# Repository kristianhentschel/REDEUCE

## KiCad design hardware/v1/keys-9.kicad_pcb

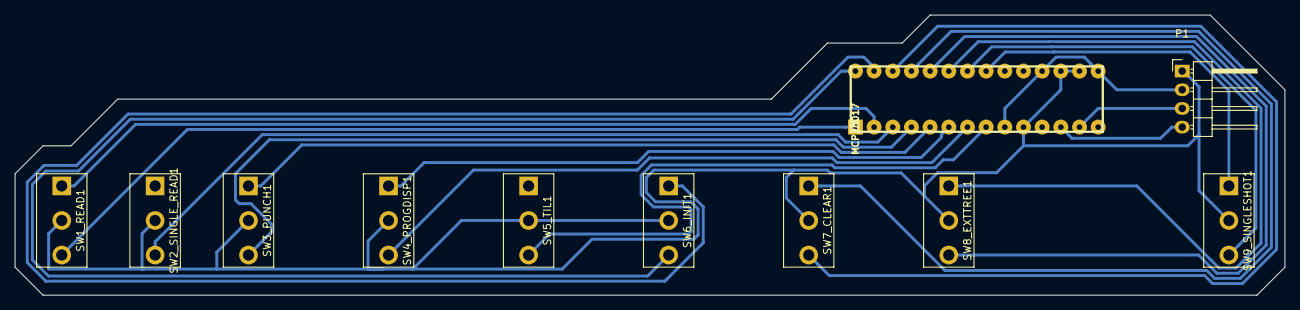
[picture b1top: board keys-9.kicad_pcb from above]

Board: 2 copper layers, 172.7 x 38.1 mm, 11 parts (0 on the bottom side), 20 nets.

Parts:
P1: CONN_01X04; Pin_Header_Angled_1x04
SW1_READ1, SW2_SINGLE_READ1, SW3_PUNCH1, SW4_PROGDISP1, SW5_TIL1, SW6_INIT1, SW7_CLEAR1, SW8_EXTTREE1, SW9_SINGLESHOT1: SWITCH_INV; SW_SPDT-custom
U1: MCP23017; DIL28

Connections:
/CLEAR_A: SW7_CLEAR1.3, U1.26
/CLEAR_B: SW7_CLEAR1.1, U1.25
/EXTREE_A: SW8_EXTTREE1.1, U1.23
/EXTREE_B: SW8_EXTTREE1.3, U1.24
/INIT_A: SW6_INIT1.1, U1.27
/INIT_B: SW6_INIT1.3, U1.28
/PROGDISP_A: SW4_PROGDISP1.3, U1.7
/PROGDISP_B: SW4_PROGDISP1.1, U1.6
/PUNCH_A: SW3_PUNCH1.1, U1.5
/PUNCH_B: SW3_PUNCH1.3, U1.4
/READ_A: SW1_READ1.1, U1.2
/READ_B: SW1_READ1.3, U1.1
/SCK: P1.4, U1.12
/SDA: P1.3, U1.13
/SINGLE_A: SW9_SINGLESHOT1.1, U1.21
/SINGLE_B: SW9_SINGLESHOT1.3, U1.22
/SREAD_DOWN: SW2_SINGLE_READ1.3, U1.3
/TIL_DOWN: SW5_TIL1.3, U1.8
GND: P1.1, SW1_READ1.2, SW2_SINGLE_READ1.2, SW3_PUNCH1.2, SW4_PROGDISP1.2, SW5_TIL1.2, SW6_INIT1.2, SW7_CLEAR1.2, SW8_EXTTREE1.2, SW9_SINGLESHOT1.2, U1.10, U1.16, U1.17
VDD: P1.2, U1.9, U1.15, U1.18

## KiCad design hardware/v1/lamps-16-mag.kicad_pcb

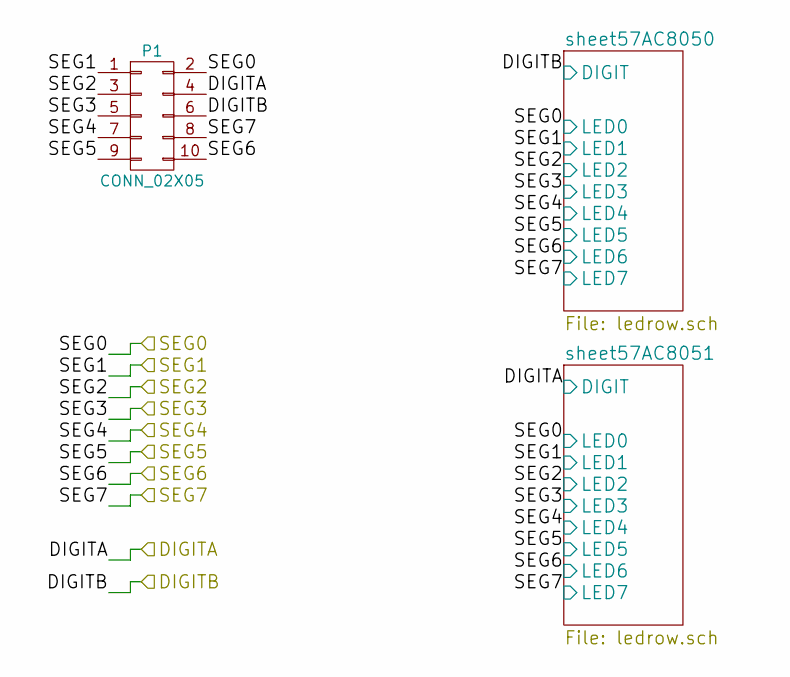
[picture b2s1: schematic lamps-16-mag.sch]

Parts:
P1: CONN_02X05; Pin_Header_Straight_2x05

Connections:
/DIGITA: P1.4; also elsewhere on the board
/DIGITB: P1.6; also elsewhere on the board
/SEG0: P1.2; also elsewhere on the board
/SEG1: P1.1; also elsewhere on the board
/SEG2: P1.3; also elsewhere on the board
/SEG3: P1.5; also elsewhere on the board
/SEG4: P1.7; also elsewhere on the board
/SEG5: P1.9; also elsewhere on the board
/SEG6: P1.10; also elsewhere on the board
/SEG7: P1.8; also elsewhere on the board

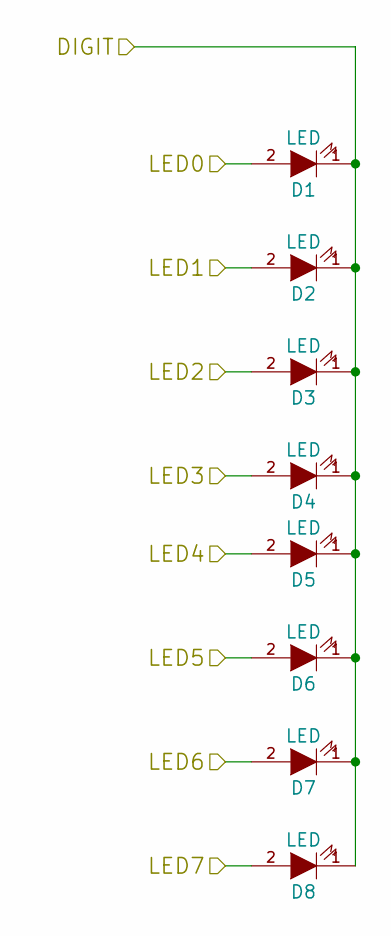
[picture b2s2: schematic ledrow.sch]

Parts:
D1, D2, D3, D4, D5, D6, D7, D8: LED; LED-5MM-custom

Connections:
/DIGITB: D1.1 (K), D2.1 (K), D3.1 (K), D4.1 (K), D5.1 (K), D6.1 (K), D7.1 (K), D8.1 (K); also elsewhere on the board
/SEG0: D1.2 (A); also elsewhere on the board
/SEG1: D2.2 (A); also elsewhere on the board
/SEG2: D3.2 (A); also elsewhere on the board
/SEG3: D4.2 (A); also elsewhere on the board
/SEG4: D5.2 (A); also elsewhere on the board
/SEG5: D6.2 (A); also elsewhere on the board
/SEG6: D7.2 (A); also elsewhere on the board
/SEG7: D8.2 (A); also elsewhere on the board

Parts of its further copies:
D9, D10, D11, D12, D13, D14, D15, D16: LED; LED-5MM-custom

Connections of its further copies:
/DIGITA: D9.1 (K), D10.1 (K), D11.1 (K), D12.1 (K), D13.1 (K), D14.1 (K), D15.1 (K), D16.1 (K); also elsewhere on the board
/SEG0: D9.2 (A); also elsewhere on the board
/SEG1: D10.2 (A); also elsewhere on the board
/SEG2: D11.2 (A); also elsewhere on the board
/SEG3: D12.2 (A); also elsewhere on the board
/SEG4: D13.2 (A); also elsewhere on the board
/SEG5: D14.2 (A); also elsewhere on the board
/SEG6: D15.2 (A); also elsewhere on the board
/SEG7: D16.2 (A); also elsewhere on the board

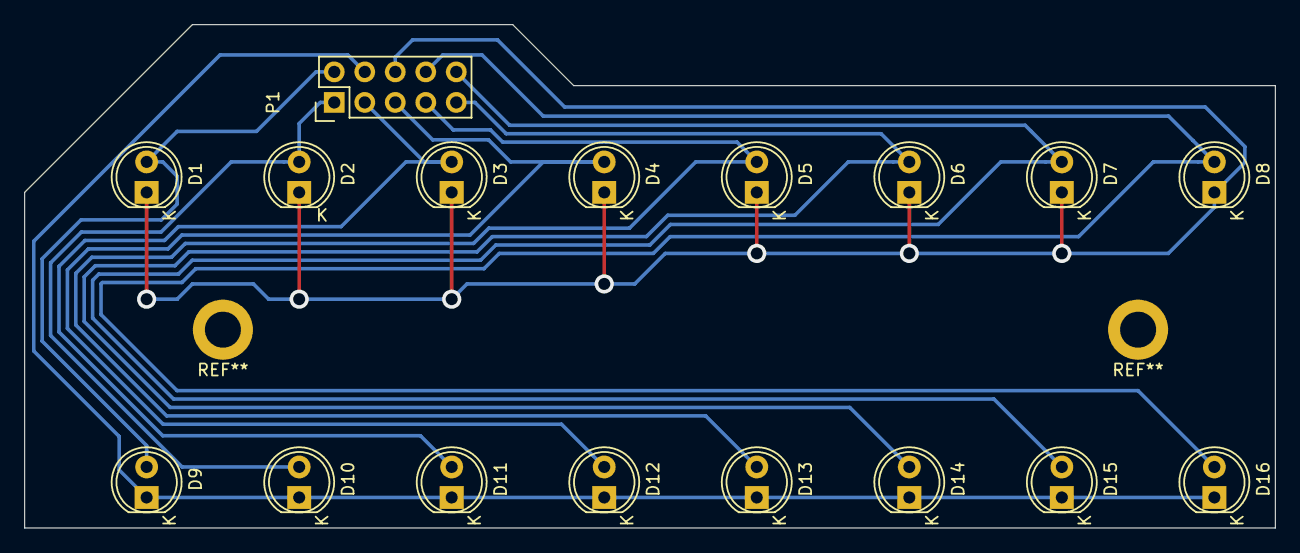
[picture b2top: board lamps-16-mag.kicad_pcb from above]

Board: 2 copper layers, 104.1 x 41.9 mm, 17 parts (0 on the bottom side), 10 nets.

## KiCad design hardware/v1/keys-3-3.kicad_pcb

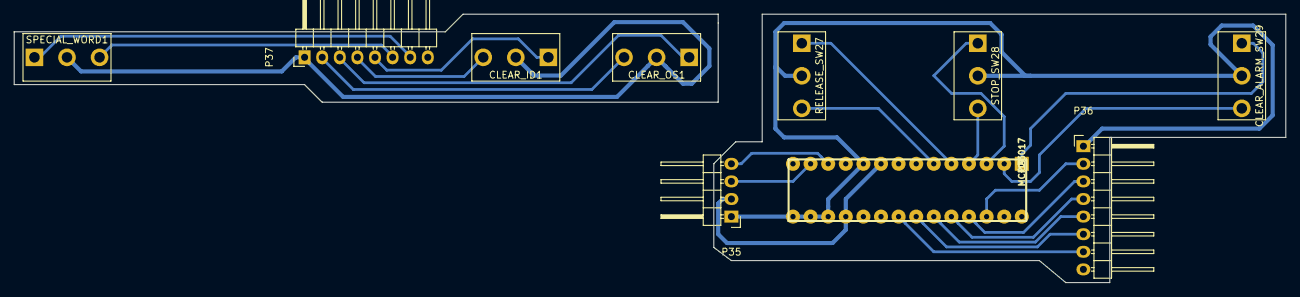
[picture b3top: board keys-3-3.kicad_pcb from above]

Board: 2 copper layers, 183.5 x 38.7 mm, 10 parts (0 on the bottom side), 23 nets.

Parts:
CLEAR_ALARM_SW29: SWITCH_INV; SW_SPDT-custom
CLEAR_ID1: SWITCH_INV; SW_SPDT-custom
CLEAR_OS1: SWITCH_INV; SW_SPDT-custom
P35: CONN_01X04; Pin_Header_Angled_1x04
P36, P37: CONN_01X08; Pin_Header_Angled_1x08
RELEASE_SW27: SWITCH_INV; SW_SPDT-custom
SPECIAL_WORD1: SWITCH_INV; SW_SPDT-custom
STOP_SW28: SWITCH_INV; SW_SPDT-custom
U9: MCP23017; DIL28

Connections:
/CLEAR_ID_A: P36.5, U9.23
/CLEAR_ID_B: P36.4, U9.24
/CLEAR_OS_A: P36.3, U9.25
/CLEAR_OS_B: P36.2, U9.26
/SCK: P35.4, U9.12
/SDA: P35.3, U9.13
/SPECIAL_A: P36.7, U9.21
/SPECIAL_B: P36.6, U9.22
GND: CLEAR_ALARM_SW29.2, P35.1, P36.1, RELEASE_SW27.2, STOP_SW28.2, U9.10, U9.15, U9.16, U9.17
unnamed: CLEAR_ALARM_SW29.1, U9.1
unnamed: CLEAR_ALARM_SW29.3, U9.2
unnamed: CLEAR_ID1.1, P37.5
unnamed: CLEAR_ID1.2, CLEAR_OS1.2, P37.1, SPECIAL_WORD1.2
unnamed: CLEAR_ID1.3, P37.4
unnamed: CLEAR_OS1.1, P37.3
unnamed: CLEAR_OS1.3, P37.2
unnamed: P37.6, SPECIAL_WORD1.3
unnamed: P37.7, SPECIAL_WORD1.1
unnamed: RELEASE_SW27.1, U9.5
unnamed: RELEASE_SW27.3, U9.6
unnamed: STOP_SW28.1, U9.3
unnamed: STOP_SW28.3, U9.4
VDD: P35.2, U9.9, U9.18

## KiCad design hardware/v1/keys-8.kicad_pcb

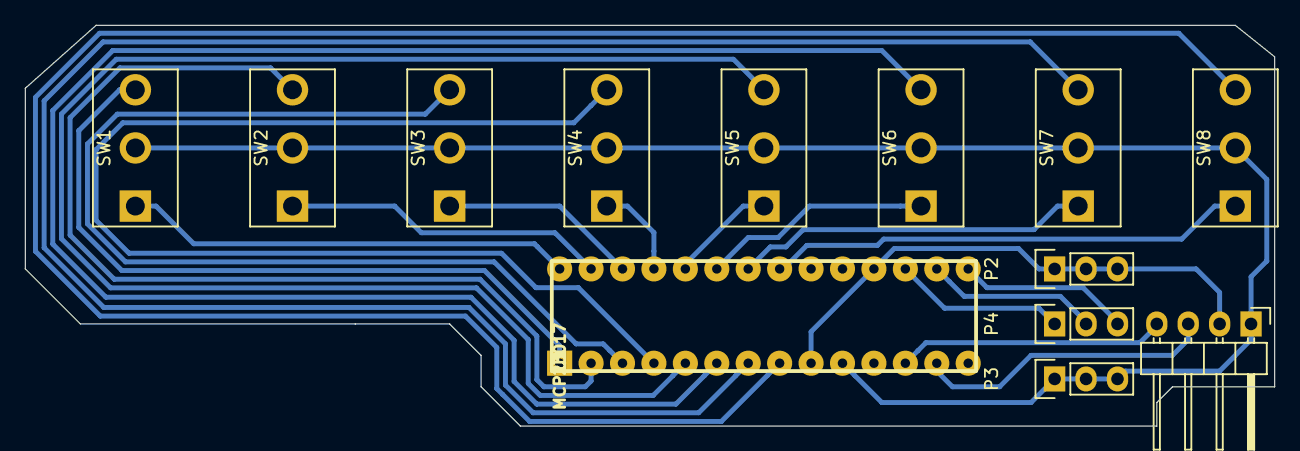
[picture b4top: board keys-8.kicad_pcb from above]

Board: 2 copper layers, 101.0 x 32.4 mm, 13 parts (0 on the bottom side), 23 nets.

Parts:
P1: CONN_01X04; Pin_Header_Angled_1x04
P2, P3, P4: CONN_01X03; Pin_Header_Straight_1x03
SW1, SW2, SW3, SW4, SW5, SW6, SW7, SW8: SWITCH_INV; SW_SPDT-custom
U1: MCP23017; DIL28

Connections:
/SCK: P1.4, U1.12
/SDA: P1.3, U1.13
GND: P1.1, P3.1, P3.2, P3.3, SW1.2, SW2.2, SW3.2, SW4.2, SW5.2, SW6.2, SW7.2, SW8.2, U1.10
unnamed: P4.1, U1.17
unnamed: P4.2, U1.16
unnamed: P4.3, U1.15
unnamed: SW1.1, U1.28
unnamed: SW1.3, U1.1
unnamed: SW2.1, U1.27
unnamed: SW2.3, U1.2
unnamed: SW3.1, U1.26
unnamed: SW3.3, U1.3
unnamed: SW4.1, U1.25
unnamed: SW4.3, U1.4
unnamed: SW5.1, U1.24
unnamed: SW5.3, U1.5
unnamed: SW6.1, U1.23
unnamed: SW6.3, U1.6
unnamed: SW7.1, U1.22
unnamed: SW7.3, U1.7
unnamed: SW8.1, U1.21
unnamed: SW8.3, U1.8
VDD: P1.2, P2.1, P2.2, P2.3, U1.9, U1.18

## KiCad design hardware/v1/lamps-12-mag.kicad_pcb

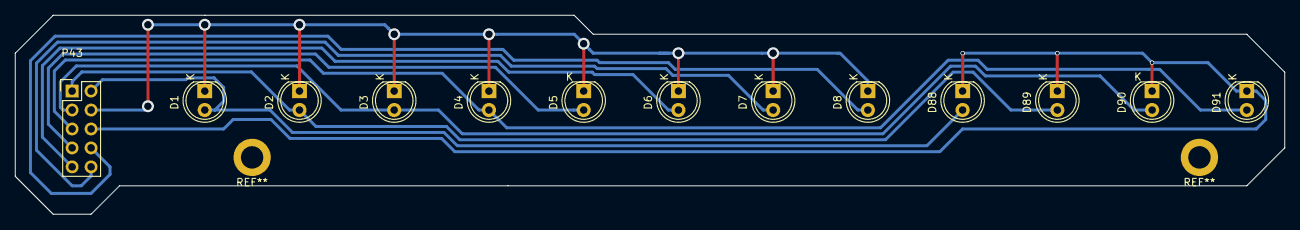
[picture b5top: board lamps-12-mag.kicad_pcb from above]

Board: 2 copper layers, 170.2 x 26.7 mm, 13 parts (0 on the bottom side), 10 nets.

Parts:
D1, D2, D3, D4, D5, D6, D7, D8, D88, D89, D90, D91: LED; LED-5MM-custom
P43: CONN_02X05; Pin_Header_Straight_2x05

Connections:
/DIGITA: D1.1, D2.1, D3.1, D4.1, D5.1, D6.1, D7.1, D8.1, P43.4
/DIGITB: D88.1, D89.1, D90.1, D91.1, P43.6
/SEG0: D1.2, D88.2, P43.2
/SEG1: D2.2, D89.2, P43.1
/SEG2: D3.2, D90.2, P43.3
/SEG3: D4.2, D91.2, P43.5
/SEG4: D5.2, P43.7
/SEG5: D6.2, P43.9
/SEG6: D7.2, P43.10
/SEG7: D8.2, P43.8

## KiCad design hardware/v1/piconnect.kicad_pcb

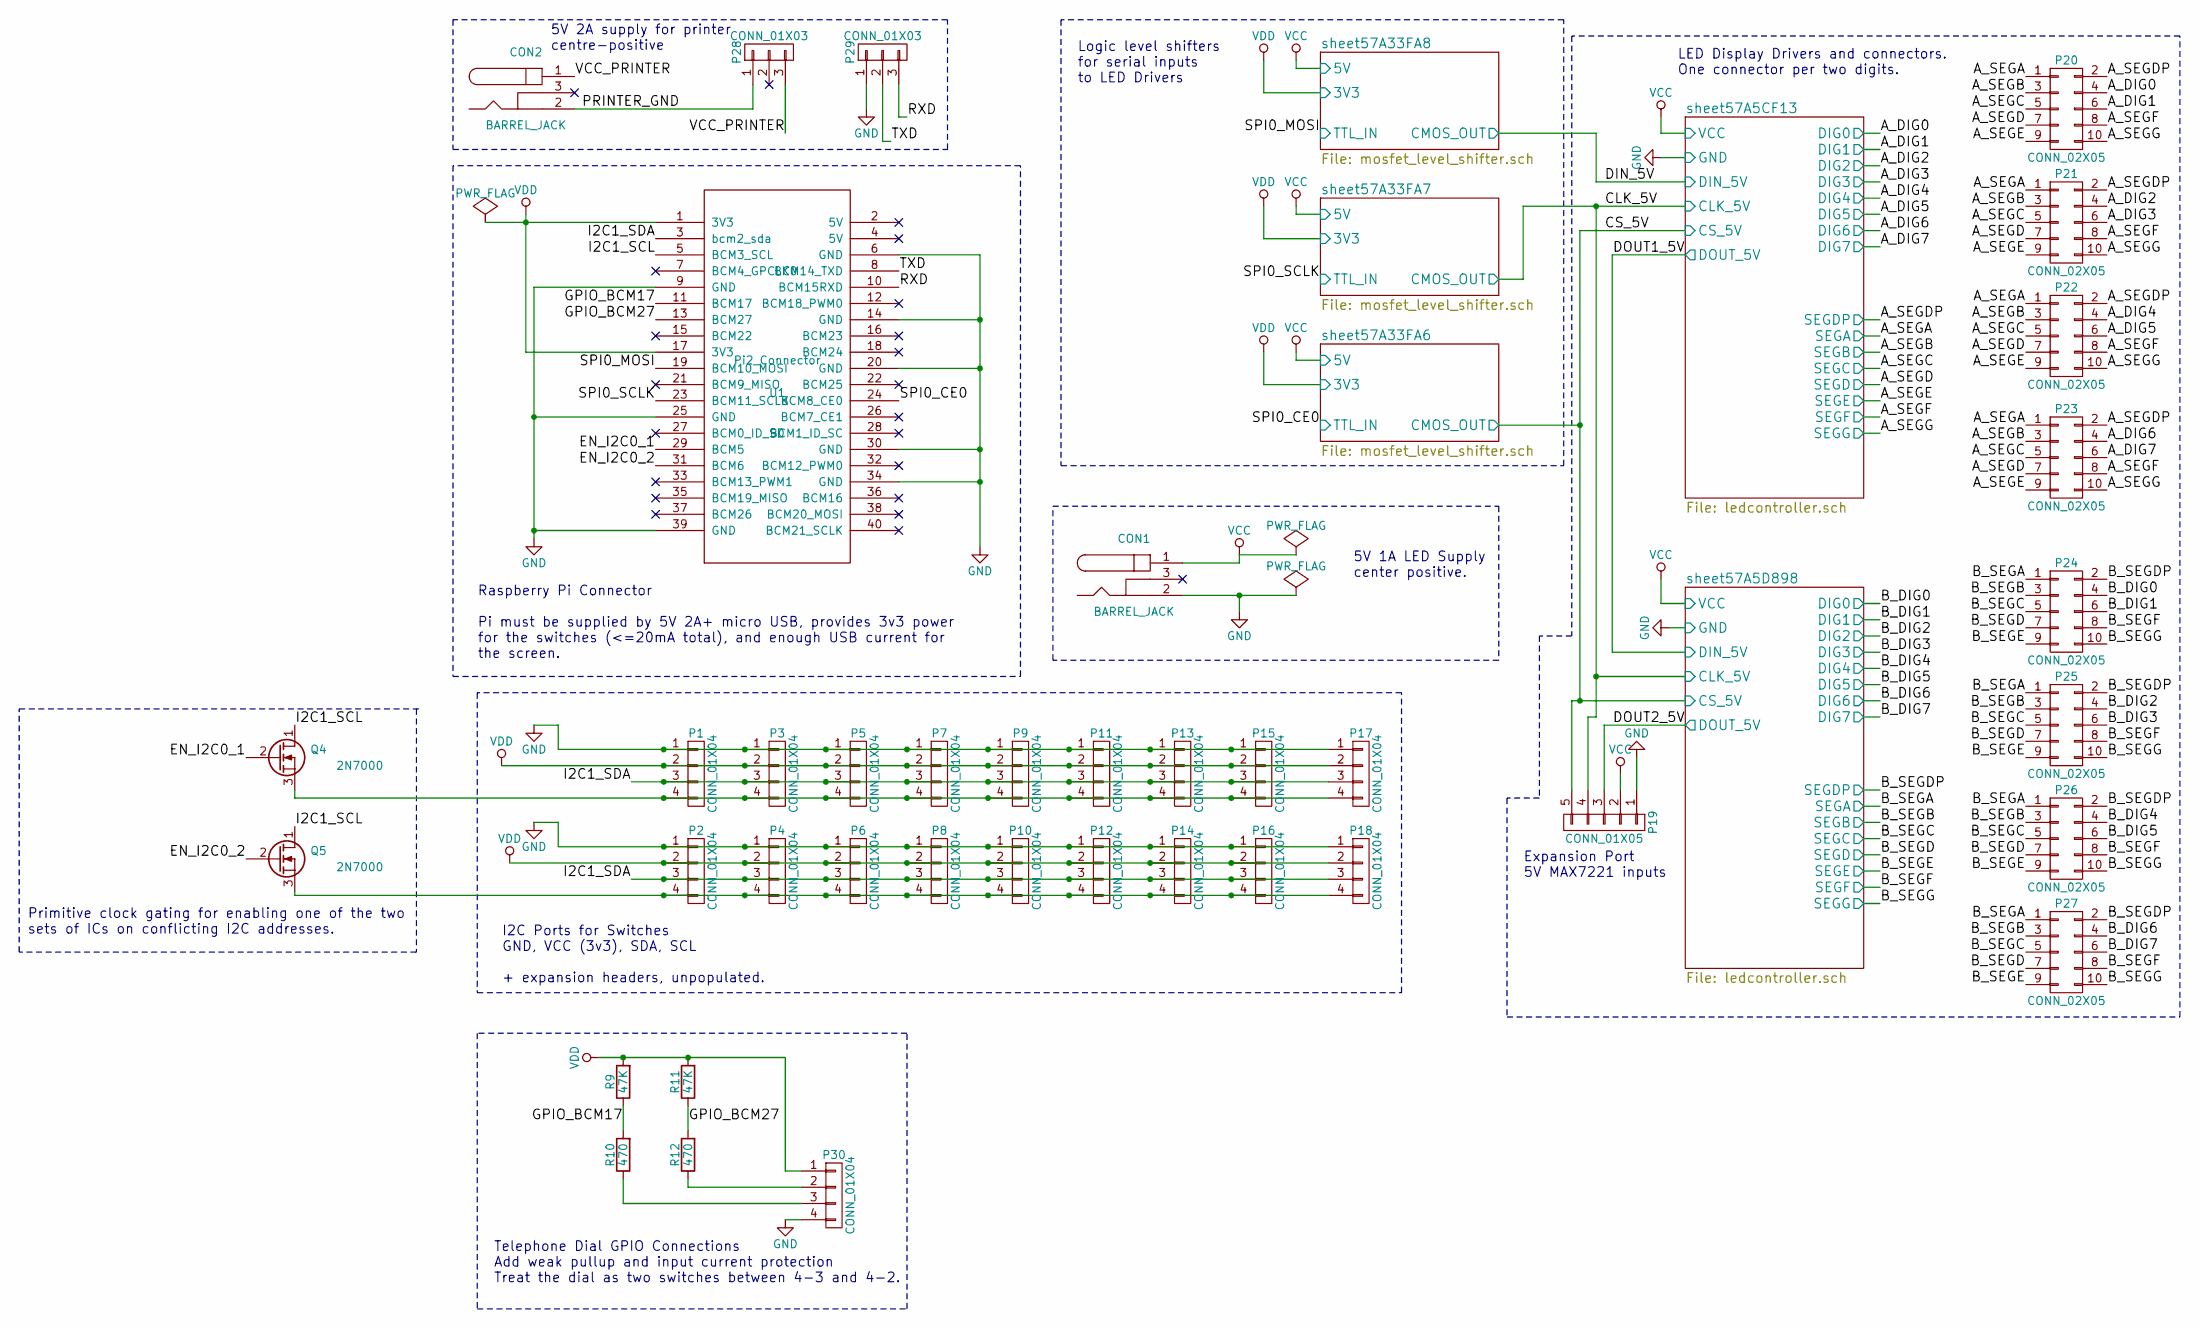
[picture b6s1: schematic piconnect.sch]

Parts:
CON1, CON2: BARREL_JACK; BARREL_JACK-custom
P1, P2, P3, P4, P5, P6, P7, P8, P9, P10, P11, P12, P13, P14, P15, P16, P17, P18, P30: CONN_01X04; Pin_Header_Straight_1x04
P19: CONN_01X05; Pin_Header_Straight_1x05
P20, P21, P22, P23, P24, P25, P26, P27: CONN_02X05; Pin_Header_Straight_2x05
P28, P29: CONN_01X03; Pin_Header_Straight_1x03
Q4, Q5: 2N7000; TO-92_Inline_Wide
R9, R11: 47K; Resistor_Horizontal_RM10mm
R10, R12: 470; Resistor_Horizontal_RM10mm
U1: Pi2_Connector; Pin_Header_Straight_2x20

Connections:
/EN_I2C0_1: Q4.2 (G), U1.29 (BCM5)
/EN_I2C0_2: Q5.2 (G), U1.31 (BCM6)
/GPIO_BCM17: R9.1, R10.2, U1.11 (BCM17)
/GPIO_BCM27: R11.1, R12.2, U1.13 (BCM27)
/I2C1_SCL: Q4.1 (D), Q5.1 (D), U1.5 (BCM3_SCL)
/I2C1_SDA: P1.3, P2.3, P3.3, P4.3, P5.3, P6.3, P7.3, P8.3, P9.3, P10.3, P11.3, P12.3, P13.3, P14.3, P15.3, P16.3, P17.3, P18.3, U1.3 (bcm2_sda)
/PRINTER_GND: CON2.2, P28.1
/RXD: P29.3, U1.10 (BCM15RXD)
/TXD: P29.2, U1.8 (BCM14_TXD)
/VCC_PRINTER: CON2.1, P28.3
/sheet57A5CF13/CLK_5V: P19.4; also elsewhere on the board
/sheet57A5CF13/DIG0: P20.4; also elsewhere on the board
/sheet57A5CF13/DIG1: P20.6; also elsewhere on the board
/sheet57A5CF13/DIG2: P21.4; also elsewhere on the board
/sheet57A5CF13/DIG3: P21.6; also elsewhere on the board
/sheet57A5CF13/DIG4: P22.4; also elsewhere on the board
/sheet57A5CF13/DIG5: P22.6; also elsewhere on the board
/sheet57A5CF13/DIG6: P23.4; also elsewhere on the board
/sheet57A5CF13/DIG7: P23.6; also elsewhere on the board
/sheet57A5CF13/SEGA: P20.1, P21.1, P22.1, P23.1; also elsewhere on the board
/sheet57A5CF13/SEGB: P20.3, P21.3, P22.3, P23.3; also elsewhere on the board
/sheet57A5CF13/SEGC: P20.5, P21.5, P22.5, P23.5; also elsewhere on the board
/sheet57A5CF13/SEGD: P20.7, P21.7, P22.7, P23.7; also elsewhere on the board
/sheet57A5CF13/SEGDP: P20.2, P21.2, P22.2, P23.2; also elsewhere on the board
/sheet57A5CF13/SEGE: P20.9, P21.9, P22.9, P23.9; also elsewhere on the board
/sheet57A5CF13/SEGF: P20.8, P21.8, P22.8, P23.8; also elsewhere on the board
/sheet57A5CF13/SEGG: P20.10, P21.10, P22.10, P23.10; also elsewhere on the board
/sheet57A5D898/DIG0: P24.4; also elsewhere on the board
/sheet57A5D898/DIG1: P24.6; also elsewhere on the board
/sheet57A5D898/DIG2: P25.4; also elsewhere on the board
/sheet57A5D898/DIG3: P25.6; also elsewhere on the board
/sheet57A5D898/DIG4: P26.4; also elsewhere on the board
/sheet57A5D898/DIG5: P26.6; also elsewhere on the board
/sheet57A5D898/DIG6: P27.4; also elsewhere on the board
/sheet57A5D898/DIG7: P27.6; also elsewhere on the board
/sheet57A5D898/DOUT_5V: P19.3; also elsewhere on the board
/sheet57A5D898/SEGA: P24.1, P25.1, P26.1, P27.1; also elsewhere on the board
/sheet57A5D898/SEGB: P24.3, P25.3, P26.3, P27.3; also elsewhere on the board
/sheet57A5D898/SEGC: P24.5, P25.5, P26.5, P27.5; also elsewhere on the board
/sheet57A5D898/SEGD: P24.7, P25.7, P26.7, P27.7; also elsewhere on the board
/sheet57A5D898/SEGDP: P24.2, P25.2, P26.2, P27.2; also elsewhere on the board
/sheet57A5D898/SEGE: P24.9, P25.9, P26.9, P27.9; also elsewhere on the board
/sheet57A5D898/SEGF: P24.8, P25.8, P26.8, P27.8; also elsewhere on the board
/sheet57A5D898/SEGG: P24.10, P25.10, P26.10, P27.10; also elsewhere on the board
/sheet57A33FA6/CMOS_OUT: P19.5; also elsewhere on the board
/sheet57A33FA6/TTL_IN: U1.24 (BCM8_CE0); also elsewhere on the board
/sheet57A33FA7/TTL_IN: U1.23 (BCM11_SCLK); also elsewhere on the board
/sheet57A33FA8/TTL_IN: U1.19 (BCM10_MOSI); also elsewhere on the board
GND: CON1.2, P1.1, P2.1, P3.1, P4.1, P5.1, P6.1, P7.1, P8.1, P9.1, P10.1, P11.1, P12.1, P13.1, P14.1, P15.1, P16.1, P17.1, P18.1, P19.1, P29.1, P30.4, U1.6 (GND), U1.9 (GND), U1.14 (GND), U1.20 (GND), U1.25 (GND), U1.30 (GND), U1.34 (GND), U1.39 (GND); also elsewhere on the board
unnamed: P1.4, P3.4, P5.4, P7.4, P9.4, P11.4, P13.4, P15.4, P17.4, Q4.3 (S)
unnamed: P2.4, P4.4, P6.4, P8.4, P10.4, P12.4, P14.4, P16.4, P18.4, Q5.3 (S)
unnamed: P30.2, R12.1
unnamed: P30.3, R10.1
VCC: CON1.1, P19.2; also elsewhere on the board
VDD: P1.2, P2.2, P3.2, P4.2, P5.2, P6.2, P7.2, P8.2, P9.2, P10.2, P11.2, P12.2, P13.2, P14.2, P15.2, P16.2, P17.2, P18.2, P30.1, R9.2, R11.2, U1.1 (3V3), U1.17 (3V3); also elsewhere on the board

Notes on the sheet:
5V 1A LED Supply center positive.
Raspberry Pi Connector Pi must be supplied by 5V 2A+ micro USB, provides 3v3 power for the switches (<=20mA total), and enough USB current for the screen.
Expansion Port 5V MAX7221 inputs
I2C Ports for Switches GND, VCC (3v3), SDA, SCL + expansion headers, unpopulated.
LED Display Drivers and connectors. One connector per two digits.
Logic level shifters for serial inputs to LED Drivers
5V 2A supply for printer centre-positive
Telephone Dial GPIO Connections Add weak pullup and input current protection Treat the dial as two switches between 4-3 and 4-2.
Primitive clock gating for enabling one of the two sets of ICs on conflicting I2C addresses.

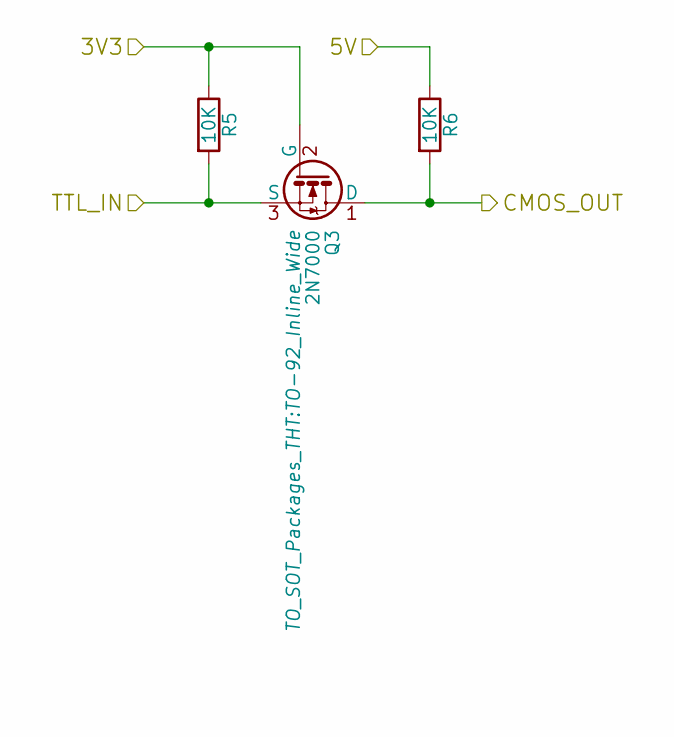
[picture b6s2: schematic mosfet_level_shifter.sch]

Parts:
Q1: 2N7000; TO-92_Inline_Wide
R1, R2: 10K; Resistor_Horizontal_RM10mm

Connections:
/sheet57A33FA6/CMOS_OUT: Q1.1 (D), R2.2; also elsewhere on the board
/sheet57A33FA6/TTL_IN: Q1.3 (S), R1.2; also elsewhere on the board
VCC: R2.1; also elsewhere on the board
VDD: Q1.2 (G), R1.1; also elsewhere on the board

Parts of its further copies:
Q2, Q3: 2N7000; TO-92_Inline_Wide
R3, R4, R5, R6: 10K; Resistor_Horizontal_RM10mm

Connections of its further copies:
/sheet57A5CF13/CLK_5V: Q2.1 (D), R4.2; also elsewhere on the board
/sheet57A33FA7/TTL_IN: Q2.3 (S), R3.2; also elsewhere on the board
/sheet57A33FA8/CMOS_OUT: Q3.1 (D), R6.2; also elsewhere on the board
/sheet57A33FA8/TTL_IN: Q3.3 (S), R5.2; also elsewhere on the board
VCC: R4.1, R6.1; also elsewhere on the board
VDD: Q2.2 (G), Q3.2 (G), R3.1, R5.1; also elsewhere on the board

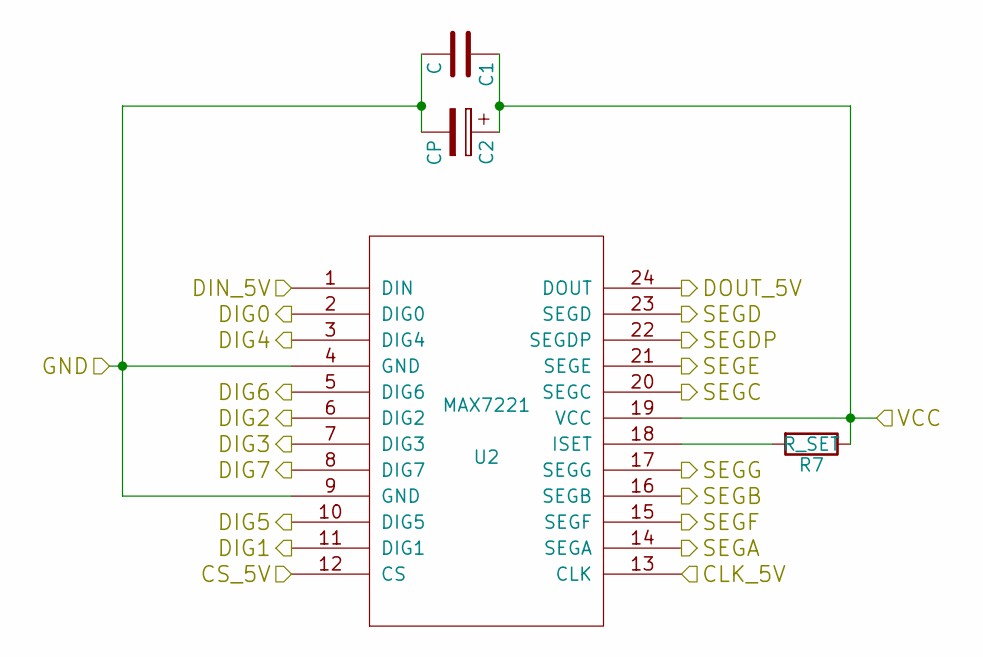
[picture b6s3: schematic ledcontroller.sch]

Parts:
C1: C; C_Disc_D6_P5
C2: CP; C_Radial_D5_L11_P2
R7: R_SET; Resistor_Horizontal_RM10mm
U2: MAX7221; DIL24

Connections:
/sheet57A5CF13/CLK_5V: U2.13 (CLK); also elsewhere on the board
/sheet57A5CF13/DIG0: U2.2 (DIG0); also elsewhere on the board
/sheet57A5CF13/DIG1: U2.11 (DIG1); also elsewhere on the board
/sheet57A5CF13/DIG2: U2.6 (DIG2); also elsewhere on the board
/sheet57A5CF13/DIG3: U2.7 (DIG3); also elsewhere on the board
/sheet57A5CF13/DIG4: U2.3 (DIG4); also elsewhere on the board
/sheet57A5CF13/DIG5: U2.10 (DIG5); also elsewhere on the board
/sheet57A5CF13/DIG6: U2.5 (DIG6); also elsewhere on the board
/sheet57A5CF13/DIG7: U2.8 (DIG7); also elsewhere on the board
/sheet57A5CF13/SEGA: U2.14 (SEGA); also elsewhere on the board
/sheet57A5CF13/SEGB: U2.16 (SEGB); also elsewhere on the board
/sheet57A5CF13/SEGC: U2.20 (SEGC); also elsewhere on the board
/sheet57A5CF13/SEGD: U2.23 (SEGD); also elsewhere on the board
/sheet57A5CF13/SEGDP: U2.22 (SEGDP); also elsewhere on the board
/sheet57A5CF13/SEGE: U2.21 (SEGE); also elsewhere on the board
/sheet57A5CF13/SEGF: U2.15 (SEGF); also elsewhere on the board
/sheet57A5CF13/SEGG: U2.17 (SEGG); also elsewhere on the board
/sheet57A5D898/DIN_5V: U2.24 (DOUT); also elsewhere on the board
/sheet57A33FA6/CMOS_OUT: U2.12 (CS); also elsewhere on the board
/sheet57A33FA8/CMOS_OUT: U2.1 (DIN); also elsewhere on the board
GND: C1.2, C2.2, U2.4 (GND), U2.9 (GND); also elsewhere on the board
unnamed: R7.2, U2.18 (ISET)
VCC: C1.1, C2.1, R7.1, U2.19 (VCC); also elsewhere on the board

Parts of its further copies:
C3: C; C_Disc_D6_P5
C4: CP; C_Radial_D5_L11_P2
R8: R_SET; Resistor_Horizontal_RM10mm
U3: MAX7221; DIL24

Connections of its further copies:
/sheet57A5CF13/CLK_5V: U3.13 (CLK); also elsewhere on the board
/sheet57A5D898/DIG0: U3.2 (DIG0); also elsewhere on the board
/sheet57A5D898/DIG1: U3.11 (DIG1); also elsewhere on the board
/sheet57A5D898/DIG2: U3.6 (DIG2); also elsewhere on the board
/sheet57A5D898/DIG3: U3.7 (DIG3); also elsewhere on the board
/sheet57A5D898/DIG4: U3.3 (DIG4); also elsewhere on the board
/sheet57A5D898/DIG5: U3.10 (DIG5); also elsewhere on the board
/sheet57A5D898/DIG6: U3.5 (DIG6); also elsewhere on the board
/sheet57A5D898/DIG7: U3.8 (DIG7); also elsewhere on the board
/sheet57A5D898/DIN_5V: U3.1 (DIN); also elsewhere on the board
/sheet57A5D898/DOUT_5V: U3.24 (DOUT); also elsewhere on the board
/sheet57A5D898/SEGA: U3.14 (SEGA); also elsewhere on the board
/sheet57A5D898/SEGB: U3.16 (SEGB); also elsewhere on the board
/sheet57A5D898/SEGC: U3.20 (SEGC); also elsewhere on the board
/sheet57A5D898/SEGD: U3.23 (SEGD); also elsewhere on the board
/sheet57A5D898/SEGDP: U3.22 (SEGDP); also elsewhere on the board
/sheet57A5D898/SEGE: U3.21 (SEGE); also elsewhere on the board
/sheet57A5D898/SEGF: U3.15 (SEGF); also elsewhere on the board
/sheet57A5D898/SEGG: U3.17 (SEGG); also elsewhere on the board
/sheet57A33FA6/CMOS_OUT: U3.12 (CS); also elsewhere on the board
GND: C3.2, C4.2, U3.4 (GND), U3.9 (GND); also elsewhere on the board
unnamed: R8.2, U3.18 (ISET)
VCC: C3.1, C4.1, R8.1, U3.19 (VCC); also elsewhere on the board

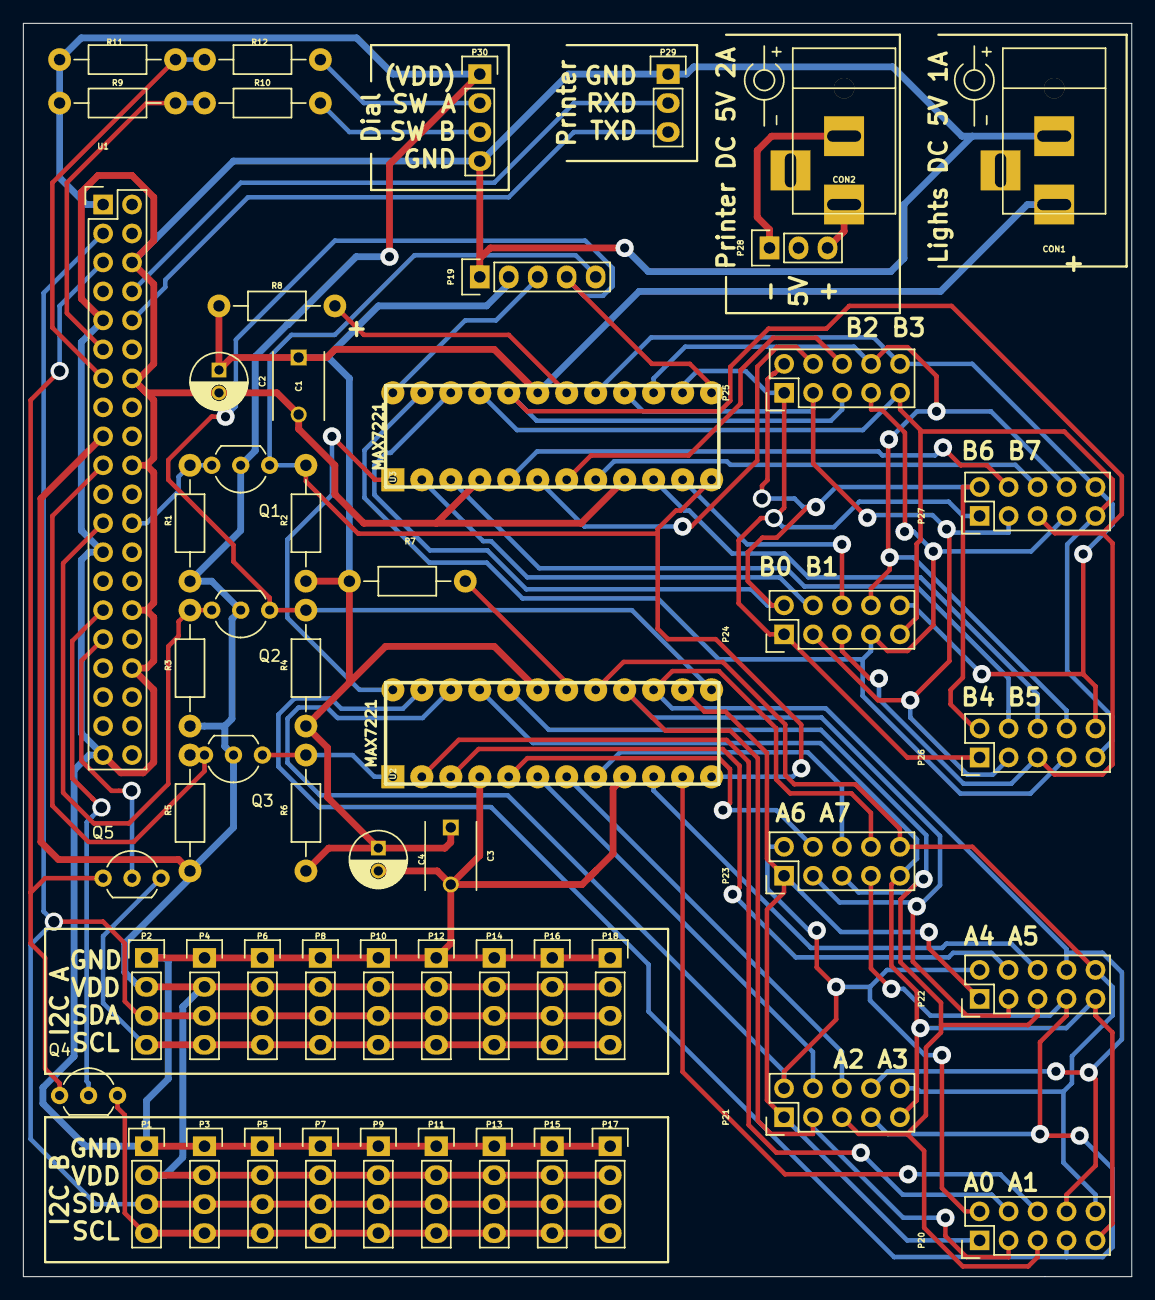
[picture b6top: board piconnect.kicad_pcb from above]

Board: 2 copper layers, 97.2 x 109.9 mm, 56 parts (0 on the bottom side), 59 nets.

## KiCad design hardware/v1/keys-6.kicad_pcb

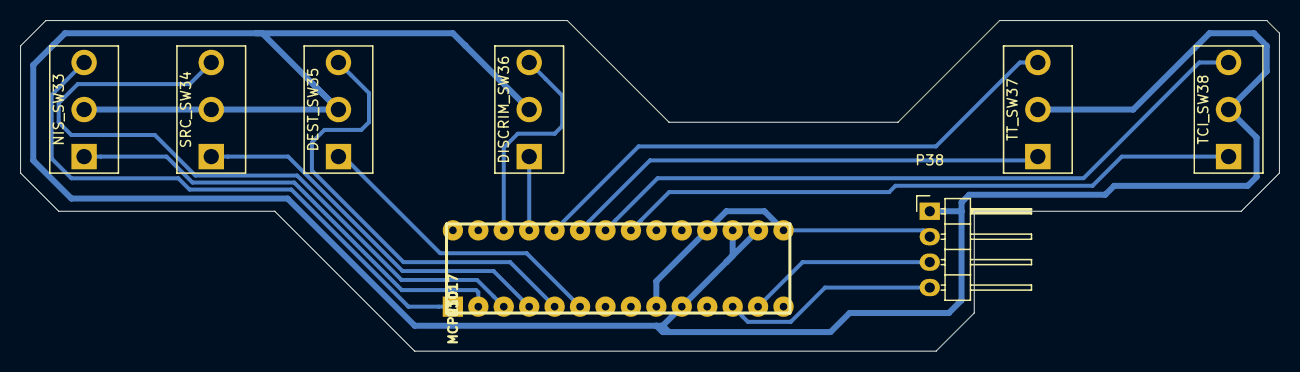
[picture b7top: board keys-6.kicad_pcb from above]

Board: 2 copper layers, 125.7 x 33.0 mm, 8 parts (0 on the bottom side), 16 nets.

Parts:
DEST_SW35: SWITCH_INV; SW_SPDT-custom
DISCRIM_SW36: SWITCH_INV; SW_SPDT-custom
NIS_SW33: SWITCH_INV; SW_SPDT-custom
P38: CONN_01X04; Pin_Header_Angled_1x04
SRC_SW34: SWITCH_INV; SW_SPDT-custom
TCI_SW38: SWITCH_INV; SW_SPDT-custom
TT_SW37: SWITCH_INV; SW_SPDT-custom
U10: MCP23017; DIL28

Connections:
/DEST_A: DEST_SW35.1, U10.6
/DEST_B: DEST_SW35.3, U10.5
/DISCRIM_A: DISCRIM_SW36.1, U10.25
/DISCRIM_B: DISCRIM_SW36.3, U10.26
/NIS_A: NIS_SW33.1, U10.2
/NIS_B: NIS_SW33.3, U10.1
/SCK: P38.4, U10.12
/SDA: P38.3, U10.13
/SRC_A: SRC_SW34.1, U10.4
/SRC_B: SRC_SW34.3, U10.3
/TCI_A: TCI_SW38.1, U10.21
/TCI_B: TCI_SW38.3, U10.22
/TT_A: TT_SW37.1, U10.23
/TT_B: TT_SW37.3, U10.24
GND: DEST_SW35.2, DISCRIM_SW36.2, NIS_SW33.2, P38.1, SRC_SW34.2, TCI_SW38.2, TT_SW37.2, U10.10, U10.16, U10.17
VDD: P38.2, U10.9, U10.15, U10.18

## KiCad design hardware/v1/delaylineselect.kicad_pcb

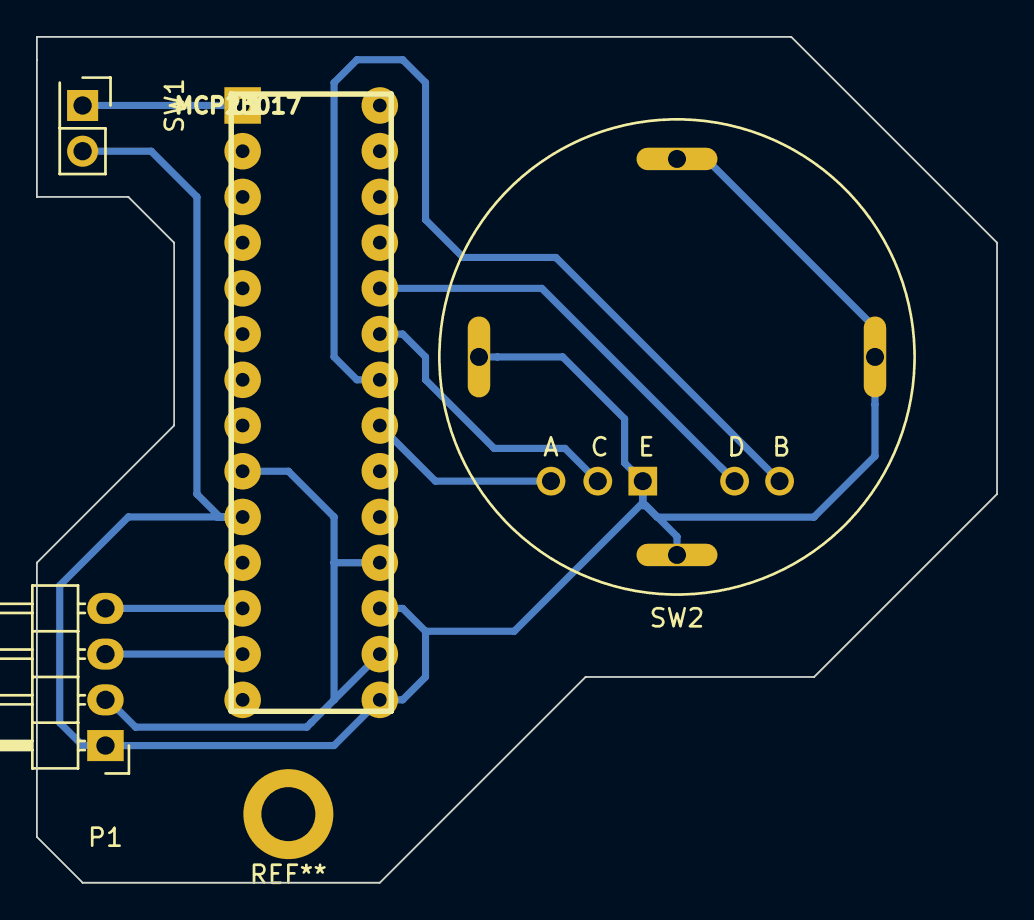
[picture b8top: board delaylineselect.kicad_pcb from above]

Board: 2 copper layers, 53.3 x 47.0 mm, 4 parts (0 on the bottom side), 9 nets.

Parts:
P1: CONN_01X04; Pin_Header_Angled_1x04
SW1: SW_PUSH; Pin_Header_Straight_2x01
SW2: Coded_Switch; ROTARY_BCK1002-custom
U1: MCP23017; DIL28

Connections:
/MCSLIP: SW1.1, U1.1
/SCK: P1.4, U1.12
/SDA: P1.3, U1.13
/SELECT_A: SW2.2, U1.21
/SELECT_B: SW2.3, U1.22
/SELECT_C: SW2.4, U1.23
/SELECT_D: SW2.5, U1.24
GND: P1.1, SW1.2, SW2.1, U1.10, U1.15, U1.17
VDD: P1.2, U1.9, U1.16, U1.18

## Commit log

2016-07-26 Add datasheets for prototype components for reference.
2016-07-26 add parts list ordered for the prototype board.
2016-07-26 Add KiCad schematic libraries and footprint modules for MAX7221 display driver, generated through http://kicad.rohrbacher.net/ .
2016-07-26 Add a prototype schematic for 64 LEDs and a MAX7221 driver. Using this to learn the PCB design software.
2016-07-26 Include the footprint modules, and assign footprints to all components.
2016-07-26 put components onto a board, still a mess.
2016-07-27 Add libraries for IO expander and Raspberry Pi connector.
2016-07-27 Move prototype circuit schematic into subfolder as it only includes the LED matrix circuit.
2016-07-27 Add pi-connected prototype schematic, with 4 switches and 16 leds, to try out component fit and IC logic.
2016-07-27 Assign footprints
2016-07-27 Add footprint fot SPDT switches according to datasheet for 100SP4T1B1M2QEH. Also attempted to route some of this complex circuit manually.
2016-07-27 Add a trivial board just fr testing hte footprints and pcb plotting process.
2016-07-27 Autoroute pi_connect project, add gerber and drill files plotted with default settings.
2016-07-28 Add corrected Pi connector footprint and re-route the prototype board.
2016-07-28 Add mosfet datasheet (for level shifter)
2016-07-28 Add testtraces project to be used for calibrating pcb plotter.
2016-08-03 Add a trivial double sided board to test PCB machine.
2016-08-03 Increased trace and via diameter size
2016-08-03 Rerouted pi connect prototype for a slightly smaller board.
2016-08-04 Add plans for PCB layout and production.
2016-08-04 Add some basic elements for v1 pcbs, such as 16-led-rows and drivers.
2016-08-04 Some autorouting on 16led row
2016-08-04 More routing experiments.
2016-08-05 Manually route lmaps-16 board
2016-08-05 Correct lamps-16 connector layout in piconnect board.
2016-08-05 Start adding pi gpio port to piconnect board.
2016-08-05 Route boards for lamps-13 and lamps-3a (one pcb file)
2016-08-05 Add switches-16 board and route it.
2016-08-05 fix missing connections in switches-16
2016-08-05 generate gerber and drill file for switches-16.
2016-08-05 Add keys-8 schematic and initial pcb layout file.
2016-08-05 Route keys-8 and generate gerber files.
2016-08-05 just moved things around a little bit
2016-08-06 Add rough layout of pcbs behind front panel.
2016-08-07 Add custom footprints with fab layer for front panel drilling outlines.
2016-08-07 replace switch footprints on keys-8
2016-08-07 slightly re-route keys-8 to shave off a few mm. Re-export gerber files and svg (edge.cuts and b.fab) to put into a new front panel cutting file.
2016-08-07 replace switch footprints in switches-16
2016-08-07 Replace LED footprints in lamps-13_3a, and delete additional unneded gerber outputs.
2016-08-07 Add new M3 drill mark pads to lamsp-13-3a
2016-08-07 Add m3 holes and re-route around them for led boards.
2016-08-07 Assign DP pin to led0 connection to match 8-bit values in MAX7221 register.
2016-08-07 Align most front panel outlines/holes and add temporary labels.
2016-08-08 Add bill of materials, coming to approx 600 pounds so far.
2016-08-08 Add labels and slightly re-arrange front panel layout.
2016-08-08 Change switch footprints, correcting the alignment pin placement
2016-08-08 Add rotary switch doc, footprint, and basic circuit
2016-08-08 Simplify routing for delaylineselect, generate gerber files and svg.
2016-08-08 Add SVG control panel processed for laser cutting:
    - convert all text to paths
    - use red (cut) and blue (score) outlines of width 0.01mm
    - check all units are in mm and 5mm margin is kept to
2016-08-09 Re-arrange switch connector pinout to simpler single-row header. Re-route the switch boards accordingly.
2016-08-09 Add mc slip, delay line select, and additional spare panels to laser cut panel file.
2016-08-09 Assigning most buttons. Still 5-6 I am very unsure about.
2016-08-09 Also export PDF from svg
2016-08-10 Mostly final label assignments with some creative license (Program display, initial input, TT, TCI, TIL)
2016-08-10 Add list of new boards to be made
2016-08-10 github markdown corrections
2016-08-10 Add new schematics for additional switch boards
2016-08-10 Integrate first set of switches
2016-08-10 Add keys-6 board and add to front panel drawing.
2016-08-10 Add Keys-9
2016-08-10 SVG now has all boards placed and updated. added the last lamps.
2016-08-11 Correct dial size (sources say 3 inch or 78mm - settled for 77 now), and reduce size of board for lights-4-3 (4 part).
2016-08-11 Add pcbs and cutouts for magnetic drum store status lamps (not labelled).
2016-08-11 Add processed files ready for laser cutting.
2016-08-11 Correct mistake on laser cutting file, add parts order list.
2016-08-12 Correct footprints for barrel connector and rotary switch.
2016-08-12 Complete piconnect circuit and start routing.
2016-08-12 Finish routing of piconnect board and generate gerber files
2016-08-12 Add gerber files for all boards to be potentially made by ragworm.
2016-08-12 Generate additional gerber files for switches-16.
2016-08-13 Add mosfet clock gates to I2C connector rows - because addresses conflict and the second bus (I2C0) cannot be used safely on the raspberry pi.
2016-08-29 Export all switches v1.1 gerber files again because silkscreen and mask were missing.
2016-08-29 Make rotary switch footprint use circular holes for compatibility with PCB machine software.
2016-08-29 correct last oval hole in delaylineselect
2016-08-30 Add outline for hardware interface demo programs
2016-08-30 (Untested) implementation for lamps interface example.
2016-08-31 start writing switches demo
2016-08-31 add driversandbox board for software testing of piconnect board.
2016-08-31 add more to switches script - still untested.
2016-09-01 Update installation instructions for hardware interface with corrected list of system packages to install.
2016-09-01 Switches working with two devices on different channels on breadboard with pi1 (may need enable pin numbers changed!)
2016-09-01 lamps demo script working on pi1 with one digit, one device on breadboard.
2016-09-01 Add printer example
2016-09-01 Add notes and cost spreadsheet
2016-09-01 Add additional datasheets for printer and HDMI screen
2016-09-01 reformatted the piconnect board for printing
2016-09-02 Initialize pullups and direction for _all_ bits in the io expanders
2016-09-02 Add a PDF document with exported PCBs for identification and assembly instructions
2017-03-04 directory for example programs
2017-03-04 Adding basic build script
2017-03-04 Fix MemoryTests
2017-03-04 Moving tests cards to their own directory
2017-03-04 Fix resource paths for test cards
2017-03-04 a basic disassembler for .CRD files. Run with java uk.ac.glasgow.redeuce.asm.Disassembler file.crd
2017-03-04 Moving squares to cards directory
2017-03-04 gradle files ignored
2017-03-04 Adding lots of example Punch-card programs for DEUCE - see http://www.pilotaceonline.com/ for details
2017-03-04 added author tag
2017-03-04 Adding basic drawing functionality
2017-03-04 Add display Reg printing
2017-03-04 Reading screen data from file
2017-03-04 Get datafile on startup
2017-03-04 Add readme for display
2017-03-04 Adding test data for display
2017-03-04 Add ability to kill full_screen display
2017-03-04 test program in DEUCE assembler
2017-03-04 DEUCE assembler
